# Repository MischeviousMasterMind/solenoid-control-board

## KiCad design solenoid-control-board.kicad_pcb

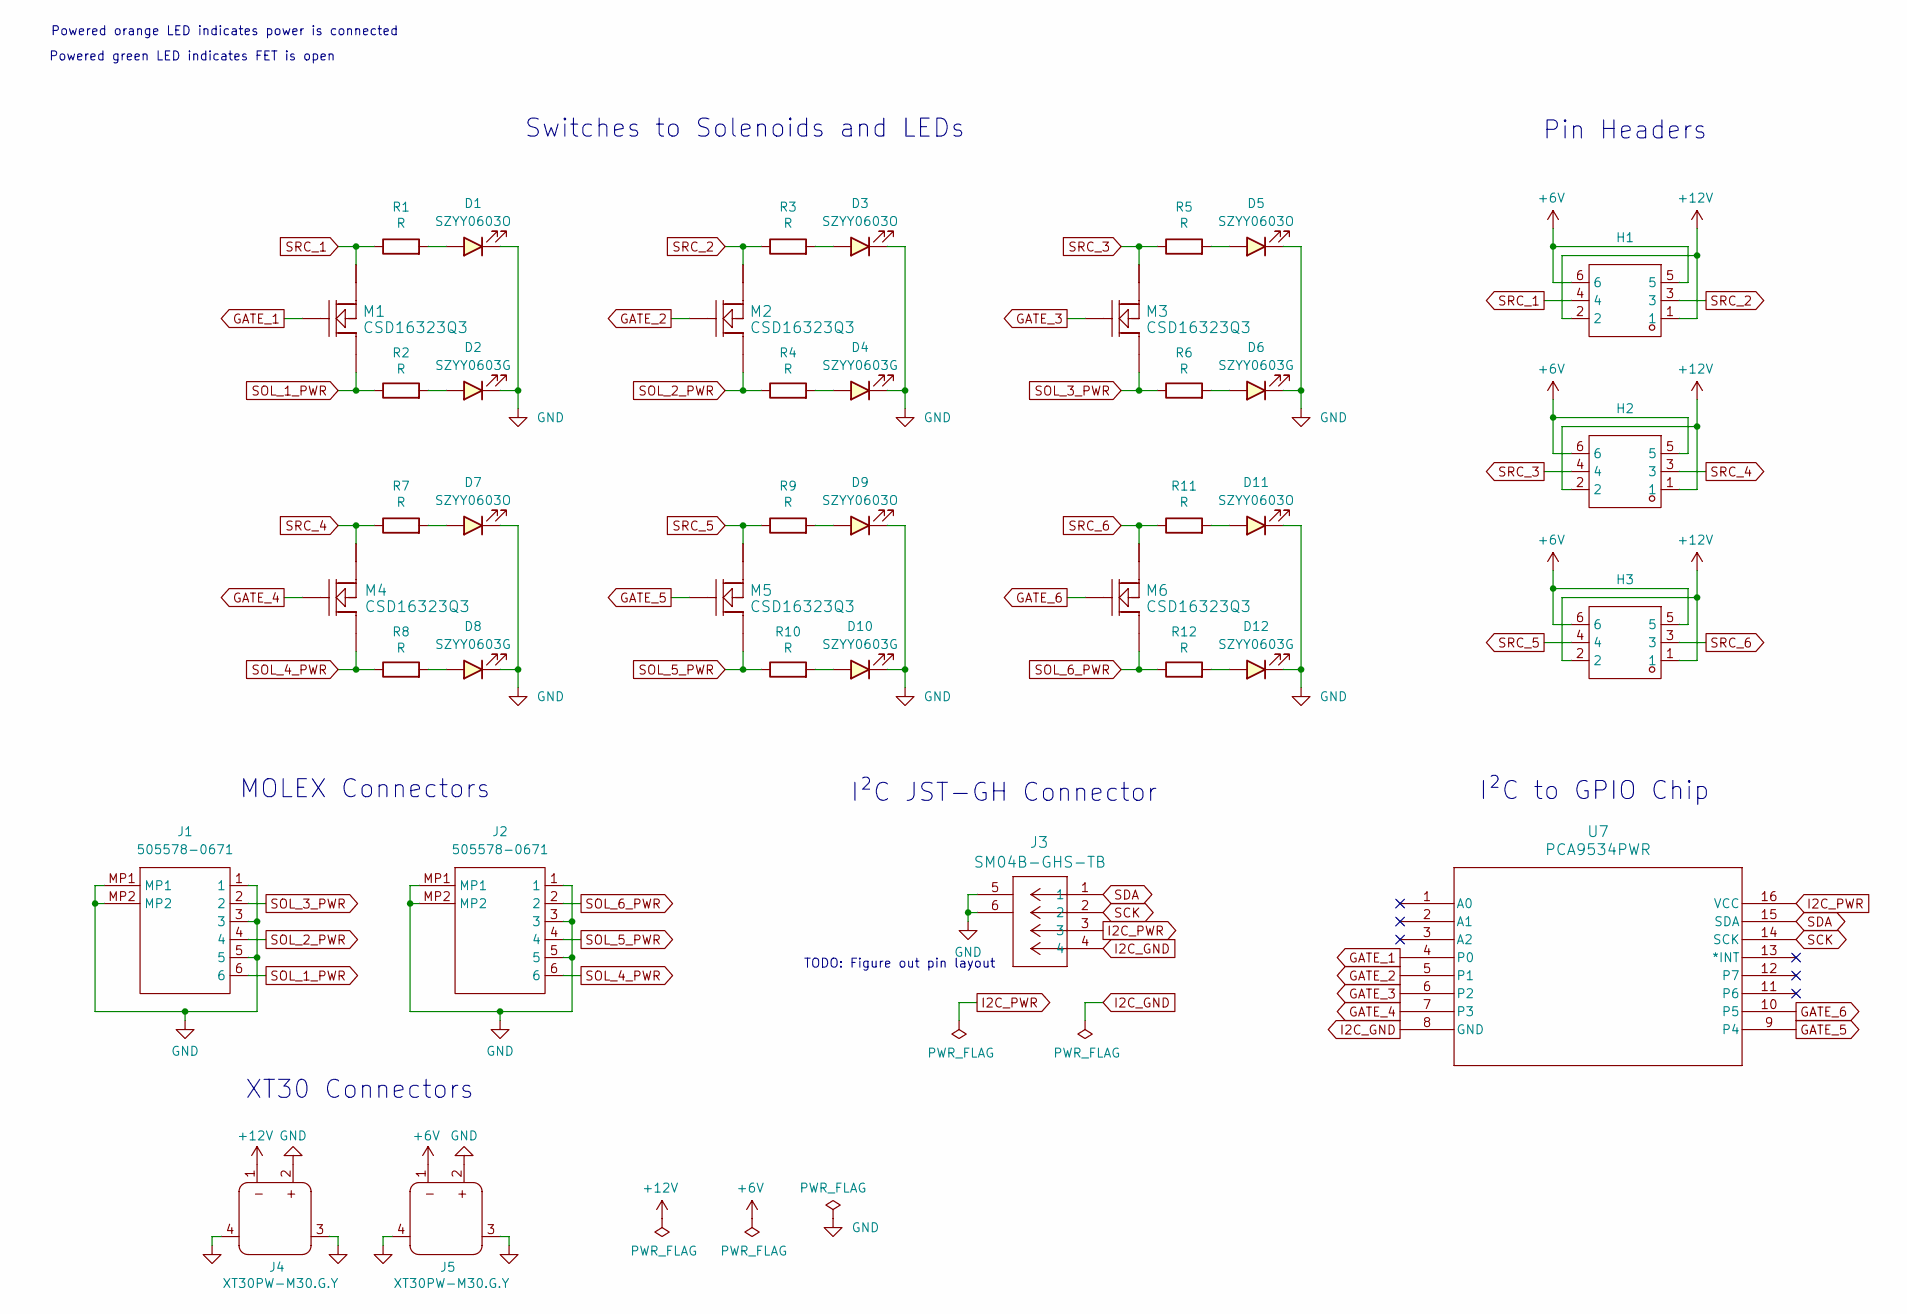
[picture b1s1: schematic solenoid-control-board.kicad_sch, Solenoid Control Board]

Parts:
D1, D3, D5, D7, D9, D11: SZYY0603O; LED0603-R-RD_ORANGE; LCSC C434425
D2, D4, D6, D8, D10, D12: SZYY0603G; LED0603-R-RD_GREEN; LCSC C19712532
H1, H2, H3: HX PZ2.54-2x3P ZZ; HDR-TH_6P-P2.54-V-M-R2-C3-S2.54-2; Manufacturer Part HX PZ2.54-2x3P ZZ; LCSC Part Name 2x3P 间距:2.54mm 方针 直插
J1, J2: 505578-0671; 5055780671; LCSC C5362280
J3: SM04B-GHS-TB; CONN_SM04B-GHS-TB_JST; LCSC C189895
J4, J5: XT30PW-M30.G.Y; CONN-TH_XT30PW-M; LCSC C431092
M1, M2, M3, M4, M5, M6: CSD16323Q3; TRANS_CSD17308Q3; LCSC C248610
R1, R2, R3, R4, R5, R6, R7, R8, R9, R10, R11, R12: R; RESC1607X60N; LCSC C99782
U7: PCA9534PWR; PW16; LCSC C133803

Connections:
+6V: H1.5, H1.6, H2.5, H2.6, H3.5, H3.6, J5.1
+12V: H1.1, H1.2, H2.1, H2.2, H3.1, H3.2, J4.1
GATE_1: M1.1, U7.4 (P0)
GATE_2: M2.1, U7.5 (P1)
GATE_3: M3.1, U7.6 (P2)
GATE_4: M4.1, U7.7 (P3)
GATE_5: M5.1, U7.9 (P4)
GATE_6: M6.1, U7.10 (P5)
GND: D1.2, D2.2, D3.2, D4.2, D5.2, D6.2, D7.2, D8.2, D9.2, D10.2, D11.2, D12.2, J1.1, J1.3, J1.5, J1.MP1, J1.MP2, J2.1, J2.3, J2.5, J2.MP1, J2.MP2, J3.5, J3.6, J4.2, J4.3, J4.4, J5.2, J5.3, J5.4
I2C_GND: J3.4, U7.8 (GND)
I2C_PWR: J3.3, U7.16 (VCC)
unnamed: D1.1, R1.2
unnamed: D2.1, R2.2
unnamed: D3.1, R3.2
unnamed: D4.1, R4.2
unnamed: D5.1, R5.2
unnamed: D6.1, R6.2
unnamed: D7.1, R7.2
unnamed: D8.1, R8.2
unnamed: D9.1, R9.2
unnamed: D10.1, R10.2
unnamed: D11.1, R11.2
unnamed: D12.1, R12.2
SCK: J3.2, U7.14 (SCK)
SDA: J3.1, U7.15 (SDA)
SOL_1_PWR: J1.6, M1.3, R2.1
SOL_2_PWR: J1.4, M2.3, R4.1
SOL_3_PWR: J1.2, M3.3, R6.1
SOL_4_PWR: J2.6, M4.3, R8.1
SOL_5_PWR: J2.4, M5.3, R10.1
SOL_6_PWR: J2.2, M6.3, R12.1
SRC_1: H1.4, M1.2, R1.1
SRC_2: H1.3, M2.2, R3.1
SRC_3: H2.4, M3.2, R5.1
SRC_4: H2.3, M4.2, R7.1
SRC_5: H3.4, M5.2, R9.1
SRC_6: H3.3, M6.2, R11.1

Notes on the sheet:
Pin Headers
Powered orange LED indicates power is connected
Switches to Solenoids and LEDs
MOLEX Connectors
I²C JST-GH Connector
XT30 Connectors
Powered green LED indicates FET is open
I²C to GPIO Chip
TODO: Figure out pin layout

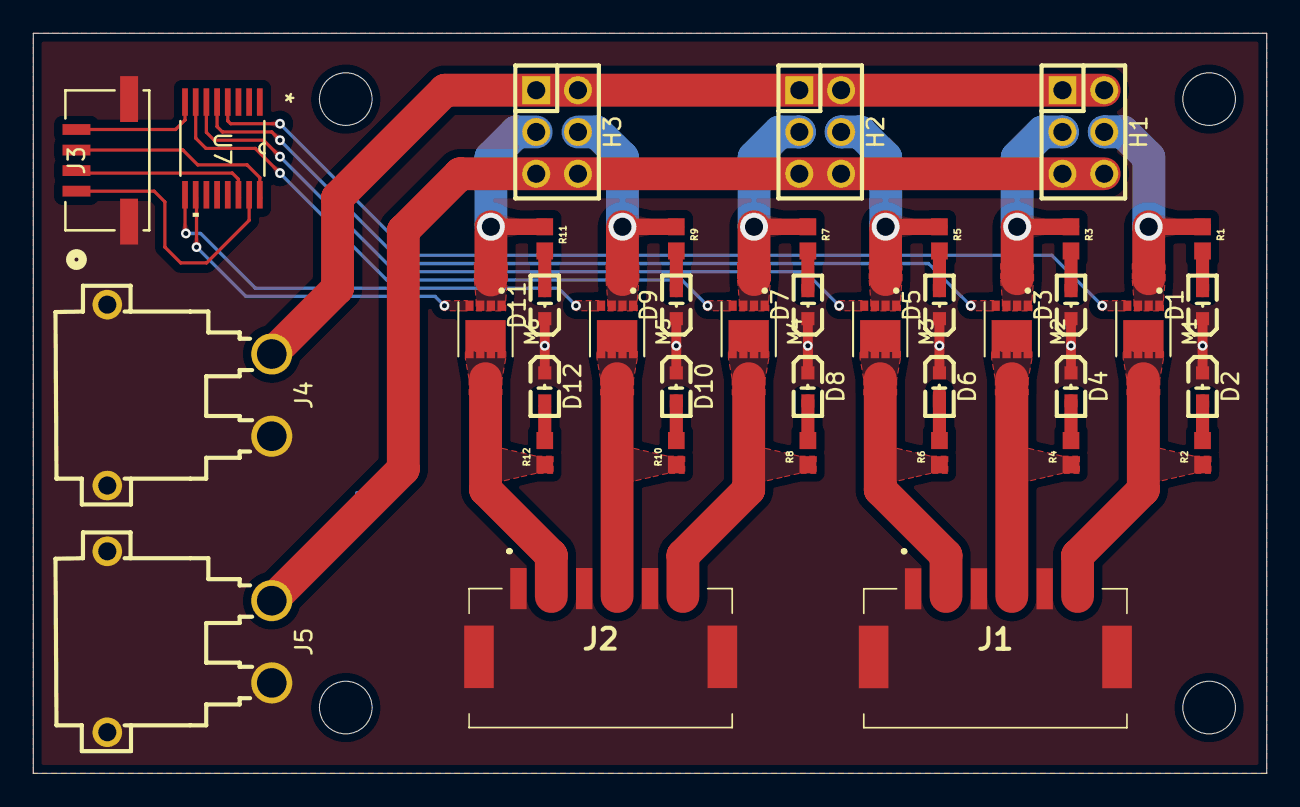
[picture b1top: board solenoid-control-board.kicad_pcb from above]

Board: 2 copper layers, 75.0 x 45.0 mm, 39 parts (0 on the bottom side), 37 nets.

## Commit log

2025-06-06 Adding footprints
2025-06-06 Test
2025-06-06 Test #2
2025-06-26 Working on layout
2025-06-28 Finished almost everything
2025-06-30 Finished layout, need to simulate
2025-07-01 Fixed DRCs
2025-07-01 Generated BOM
